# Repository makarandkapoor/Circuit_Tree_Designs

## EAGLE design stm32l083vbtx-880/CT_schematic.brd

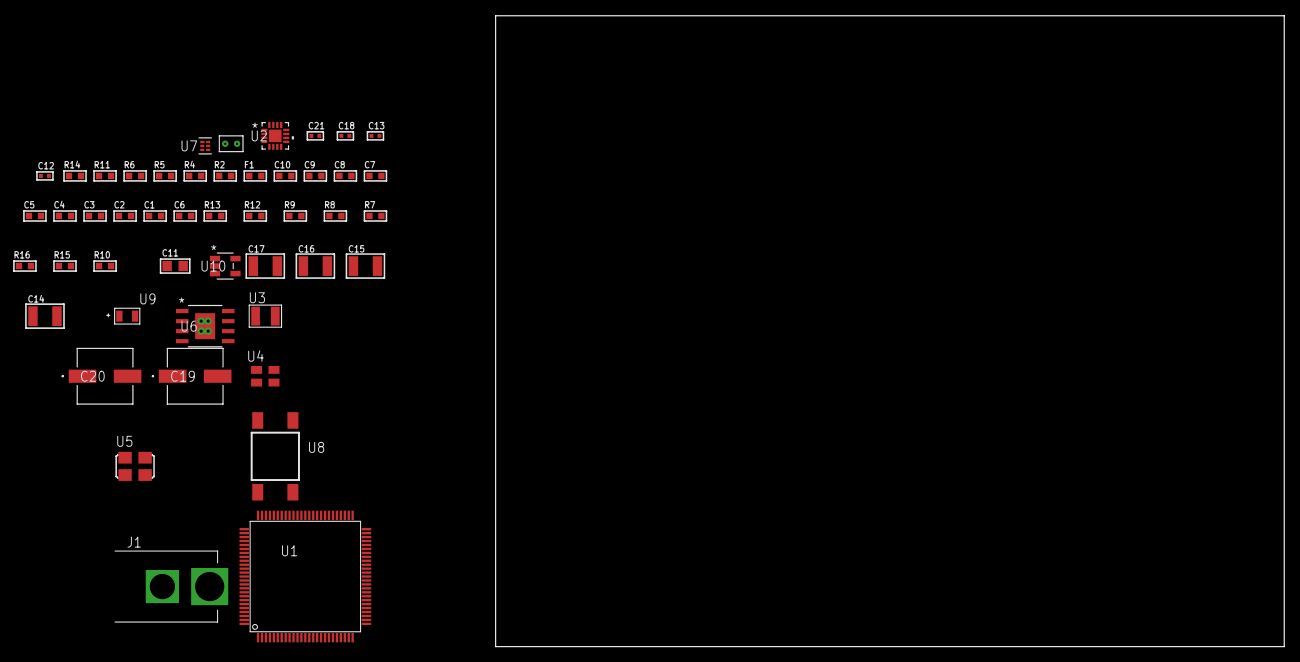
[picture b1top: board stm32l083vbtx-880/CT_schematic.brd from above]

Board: 2 copper layers, 100.0 x 80.0 mm, 48 parts (0 on the bottom side), 22 nets, no tracks yet.

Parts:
C1, C2, C3, C4, C5, C7, C10: 1e-07; C0603
C6: 4.7e-06; C0603
C8: 1e-08; C0603
C9: 1e-06; C0603
C11: 4.7e-06; C0805
C12, C13, C21: 1e-08; C0402
C14, C15, C16, C17: 1e-05; C1210
C18: 1e-07; C0402
C19, C20: 0.0001; EXV-9H
F1: 240.0; L0603
J1: PJ-037B; PJ-037B_PACKAGE
R2: 1000.0; R0603
R4: 4700.0; R0603
R5, R6, R11: 2200.0; R0603
R7, R8, R9, R12, R13: 10000.0; R0603
R10: 4031.5447154472; R0603
R14: 9100.0; R0603
R15: 680000.0; R0603
R16: 120000.0; R0603
U1: STM32L083VBT6; LQFP100
U2: M41T65Q6F; M41T65_QFN-16
U3: ABS07-32.768KHZ-7-T
U4: ASEK-32.768KHz-ECST; ASEK
U5: ASFL1-25MHZ-NCS; ASFL1
U6: MIC5234YME; SOIC-8_EP
U7: TPS3895ADRYR; SON-6
U8: 4-1437565-2; SW_4-1437565-2
U9: Q65110A2395; LGM67K-G1J2-24-Z
U10: nc7sz125m5x; NC7SZ125M5X
U11: Dummy; DUMMY_PACKAGE_100

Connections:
CLK_CRYSTAL_U2_1: U2.1, U3.1
CLK_CRYSTAL_U2_2: U2.2, U3.2
CLK_U1_8: U1.8, U4.3
CLK_U1_12: U1.12, U5.3
GND: C1.2, C2.2, C3.2, C4.2, C5.2, C6.2, C7.2, C8.2, C9.2, C10.2, C11.2, C12.2, C13.2, C14.2, C15.2, C16.2, C17.2, C18.2, C19.2, C20.2, C21.2, J1.2, R2.2, R7.2, R11.2, R14.2, R16.2, U1.19, U1.20, U1.27, U1.49, U1.74, U1.99, U2.3, U2.5, U2.17, U4.2, U5.2, U6.7, U6.EPAD, U7.2, U9.C, U10.1, U10.3, U11.1
NET_U1_6: C7.1, U1.6
NET_U1_14: R4.1, U1.14, U10.4
NET_U1_22: C8.1, C9.1, F1.1, U1.21, U1.22
NET_U1_68: R5.1, U1.68, U2.10
NET_U1_69: R6.1, U1.69, U2.9
NET_U1_94: R7.1, U1.94
NET_U1_98: U8.3, U8.4
NET_U2_4: R8.1, U2.4
NET_U2_11: R9.1, U2.11
NET_U6_4: R10.2, R11.1, U6.4
NET_U7_1: R13.1, R14.1, U7.1
NET_U7_3: R15.2, R16.1, U7.3
NET_U7_4: R12.1, U7.4, U10.2
NET_U8_1: R2.1, U8.1, U8.2
PROC_DAC_OUT2: U1.30, U11.2
VCC_S1_13V3: C14.1, C15.1, C19.1, C20.1, J1.1, U6.5, U6.8
VCC_TIER1_3V3: C1.1, C2.1, C3.1, C4.1, C5.1, C6.1, C10.1, C11.1, C12.1, C13.1, C16.1, C17.1, C18.1, C21.1, F1.2, R4.2, R5.2, R6.2, R8.2, R9.2, R10.1, R12.2, R13.2, R15.1, U1.28, U1.50, U1.73, U1.75, U1.100, U2.14, U4.4, U5.4, U6.1, U7.6, U10.5

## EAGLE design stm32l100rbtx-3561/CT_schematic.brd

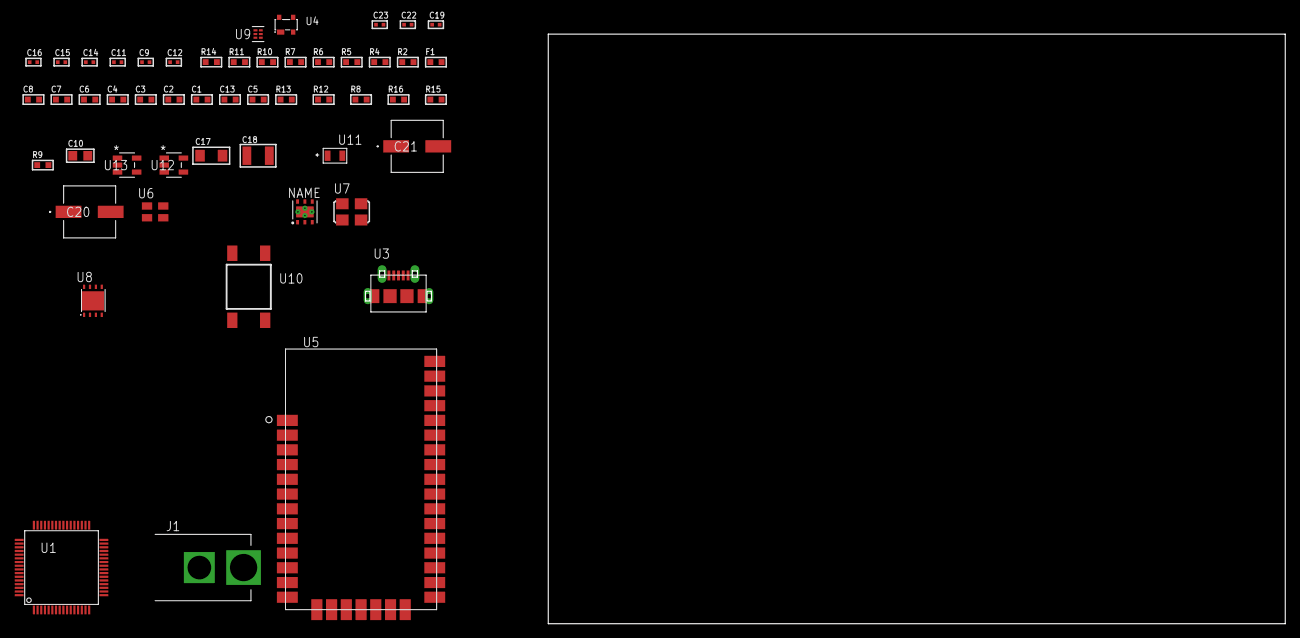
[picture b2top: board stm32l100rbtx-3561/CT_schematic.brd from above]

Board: 2 copper layers, 124.8 x 80.0 mm, 52 parts (0 on the bottom side), 27 nets, no tracks yet.

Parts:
C1, C2, C3, C4, C6: 1e-07; C0603
C5: 4.7e-06; C0603
C7: 1e-08; C0603
C8: 1e-06; C0603
C9, C14, C15, C16, C22, C23: 1e-08; C0402
C10: 1e-05; C0805
C11, C19: 1e-07; C0402
C12: 4.7e-11; C0402
C13: 8.2e-12; C0603
C17: 1e-05; C1206
C18: 1e-05; C1210
C20, C21: 0.0001; EXV-9H
F1: 240.0; L0603
J1: PJ-037B; PJ-037B_PACKAGE
R2, R11: 1000.0; R0603
R4, R5: 4700.0; R0603
R6, R7: 2200.0; R0603
R8, R12, R13: 10000.0; R0603
R9: 100000.0; R0603
R10: 2231.0; R0603
R14: 9100.0; R0603
R15: 680000.0; R0603
R16: 120000.0; R0603
U1: STM32L100RBT6; LQFP64
U2: HDC1080DMBR; WSON-6
U3: 47590-0001; MICRO_USB_AB
U4: prtr5v0u2ax; SOT143B
U5: XB24CZ7UIS-004
U6: ASEK-32.768KHz-ECST; ASEK
U7: ASFL1-25MHZ-NCS; ASFL1
U8: LP3878SDX-ADJ/NOPB; WSON-8
U9: TPS3895ADRYR; SON-6
U10: 4-1437565-2; SW_4-1437565-2
U11: Q65110A2395; LGM67K-G1J2-24-Z
U12, U13: nc7sz125m5x; NC7SZ125M5X

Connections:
CLK_U1_3: U1.3, U6.3
CLK_U1_5: U1.5, U7.3
GND: C1.2, C2.2, C3.2, C4.2, C5.2, C6.2, C7.2, C8.2, C9.2, C10.2, C11.2, C12.2, C13.2, C14.2, C15.2, C16.2, C17.2, C18.2, C19.2, C20.2, C21.2, C22.2, C23.2, J1.2, R2.2, R8.2, R11.2, R14.2, R16.2, U1.12, U1.18, U1.31, U1.47, U1.63, U2.2, U2.PAD, U3.5, U3.6, U3.7, U3.8, U3.9, U4.1, U5.1, U5.11, U5.13, U5.22, U5.35, U6.2, U7.2, U8.3, U8.PAD, U9.2, U11.C, U12.1, U12.3, U13.1, U13.3
NET_U1_1: C6.1, U1.1
NET_U1_7: R5.1, U1.7, U13.4
NET_U1_13: C7.1, C8.1, F1.1, U1.13
NET_U1_58: R6.1, U1.58, U2.6
NET_U1_59: R7.1, U1.59, U2.1
NET_U1_60: R8.1, U1.60
NET_U1_62: U10.3, U10.4
NET_U4_4: U3.1, U4.4
NET_U5_6: R4.1, U5.6, U12.4
NET_U8_1: C16.1, U8.1
NET_U8_6: R10.2, R11.1, U8.6
NET_U8_8: R9.1, U8.8
NET_U9_1: R13.1, R14.1, U9.1
NET_U9_3: R15.2, R16.1, U9.3
NET_U9_4: R12.1, U9.4, U12.2, U13.2
NET_U10_1: R2.1, U10.1, U10.2
PROC_SPI1_MISO: U1.22, U5.17
PROC_SPI1_MOSI: U1.23, U5.16
PROC_SPI1_NSS: U1.20, U5.15
PROC_SPI1_SCK: U1.21, U5.14
PROC_USB_DM: U1.44, U3.2, U4.3
PROC_USB_DP: U1.45, U3.3, U4.2
VCC_S1_5V9: C17.1, C20.1, C21.1, J1.1, R9.2, U8.4
VCC_TIER1_3V3: C1.1, C2.1, C3.1, C4.1, C5.1, C9.1, C10.1, C11.1, C12.1, C13.1, C14.1, C15.1, C18.1, C19.1, C22.1, C23.1, F1.2, R4.2, R5.2, R6.2, R7.2, R10.1, R12.2, R13.2, R15.1, U1.19, U1.32, U1.48, U1.64, U2.5, U5.2, U5.27, U6.4, U7.4, U8.5, U9.6, U12.5, U13.5

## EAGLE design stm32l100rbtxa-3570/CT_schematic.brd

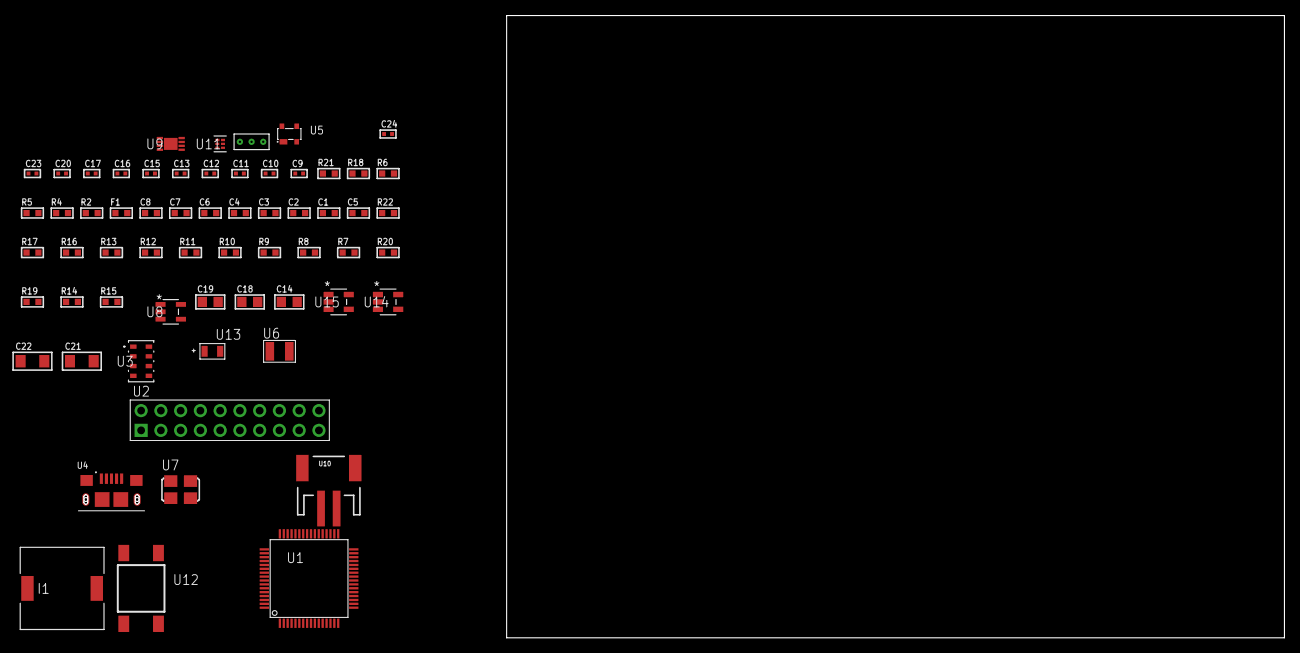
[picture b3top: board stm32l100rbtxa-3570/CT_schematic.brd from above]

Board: 2 copper layers, 154.3 x 80.0 mm, 62 parts (0 on the bottom side), 35 nets, no tracks yet.

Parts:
C1, C2, C3, C4, C6: 1e-07; C0603
C5: 4.7e-06; C0603
C7: 1e-08; C0603
C8: 1e-06; C0603
C9, C10: 1e-11; C0402
C11, C12, C13, C15, C16, C20: 1e-07; C0402
C14, C18, C19: 1e-05; C0805
C17, C23, C24: 1e-08; C0402
C21, C22: 1e-05; C1206
F1: 240.0; L0603
I1: 3.8e-06; DR1040
R2: 1000.0; R0603
R4: 4700.0; R0603
R5, R6: 2200.0; R0603
R7, R8, R9, R10, R11, R12, R13, R16, R17, R22: 10000.0; R0603
R14: 220000.0; R0603
R15: 1000000.0; R0603
R18: 9100.0; R0603
R19: 680000.0; R0603
R20: 120000.0; R0603
R21: 2000.0; R0603
U1: STM32L100RBT6A; LQFP64
U2: TST-110-05-T-D-RA
U3: MPL3115A2R1; LGA-8
U4: 10118193-0001LF; FCI_10118193-0001LF
U5: prtr5v0u2ax; SOT143B
U6: ABS07-32.768KHZ-7-T
U7: ASFL1-25MHZ-NCS; ASFL1
U8: ltc3406es5; TSOT-23-5
U9: MCP73831T-2ACI/MC; DFN8_2X3MC
U10: S2B-PH-SM4-TB(LF)(SN); JST-2-SMD
U11: TPS3895ADRYR; SON-6
U12: 4-1437565-2; SW_4-1437565-2
U13: Q65110A2395; LGM67K-G1J2-24-Z
U14, U15: nc7sz125m5x; NC7SZ125M5X
U16: Dummy; DUMMY_PACKAGE_135

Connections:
CLK_CRYSTAL_U1_3: C9.1, U1.3, U6.1
CLK_CRYSTAL_U1_4: C10.1, U1.4, U6.2
CLK_U1_5: U1.5, U7.3
GND: C1.2, C2.2, C3.2, C4.2, C5.2, C6.2, C7.2, C8.2, C9.2, C10.2, C11.2, C12.2, C13.2, C14.2, C15.2, C16.2, C17.2, C18.2, C19.1, C19.2, C20.2, C21.2, C22.2, C23.2, C24.2, R2.2, R7.2, R13.2, R14.2, R18.2, R20.2, R21.2, U1.12, U1.18, U1.31, U1.47, U1.63, U2.4, U2.6, U2.8, U2.10, U2.12, U2.14, U2.16, U2.18, U2.20, U3.3, U4.5, U4.6, U4.7, U4.8, U4.9, U5.1, U7.2, U8.2, U9.6, U9.9, U10.2, U11.2, U13.C, U14.2, U14.3, U15.1, U15.3, U16.1
INPUT_USBPOWER_5V: C21.1, R22.2, U4.1, U5.4, U9.1, U9.2
NET_U1_1: C6.1, U1.1
NET_U1_7: R4.1, U1.7, U15.4
NET_U1_13: C7.1, C8.1, F1.1, U1.13
NET_U1_58: R5.1, U1.58, U3.8
NET_U1_59: R6.1, U1.59, U3.7
NET_U1_60: R7.1, U1.60
NET_U1_62: U12.3, U12.4
NET_U2_19: R13.1, U2.19
NET_U3_2: C16.1, U3.2
NET_U8_3: I1.1, U8.3
NET_U8_5: R14.1, R15.1, U8.5
NET_U8_ATNET_3: I1.2, R15.2
NET_U9_5: R22.1, U9.5
NET_U9_8: R21.1, U9.8
NET_U11_1: R17.1, R18.1, U11.1
NET_U11_3: R19.2, R20.1, U11.3
NET_U11_4: R16.1, U11.4, U14.4, U15.2
NET_U12_1: R2.1, U12.1, U12.2
PROC_ADC_IN13: U1.11, U16.3
PROC_ADC_IN20: U1.35, U16.2
PROC_SYS_JTCK_SWCLK: R11.1, U1.49, U2.9
PROC_SYS_JTDI: R9.1, U1.50, U2.5
PROC_SYS_JTDO_TRACESWO: U1.55, U2.13
PROC_SYS_JTMS_SWDIO: R10.1, U1.46, U2.7
PROC_SYS_JTRST: R8.1, U1.56, U2.3
PROC_USB_DM: U1.44, U4.2, U5.3
PROC_USB_DP: U1.45, U4.3, U5.2
RST_OUT_U2_SRESET_B: R12.1, U2.15, U14.1
VCC_S1_3V7: C18.1, C22.1, U8.4, U9.3, U9.4, U10.1
VCC_TIER1_3V3: C1.1, C2.1, C3.1, C4.1, C5.1, C11.1, C12.1, C13.1, C14.1, C15.1, C17.1, C19.2, C20.1, C23.1, C24.1, F1.2, I1.2, R4.2, R5.2, R6.2, R8.2, R9.2, R10.2, R11.2, R12.2, R15.2, R16.2, R17.2, R19.1, U1.19, U1.32, U1.48, U1.64, U2.1, U2.2, U3.1, U3.4, U7.4, U11.6, U14.5, U15.5

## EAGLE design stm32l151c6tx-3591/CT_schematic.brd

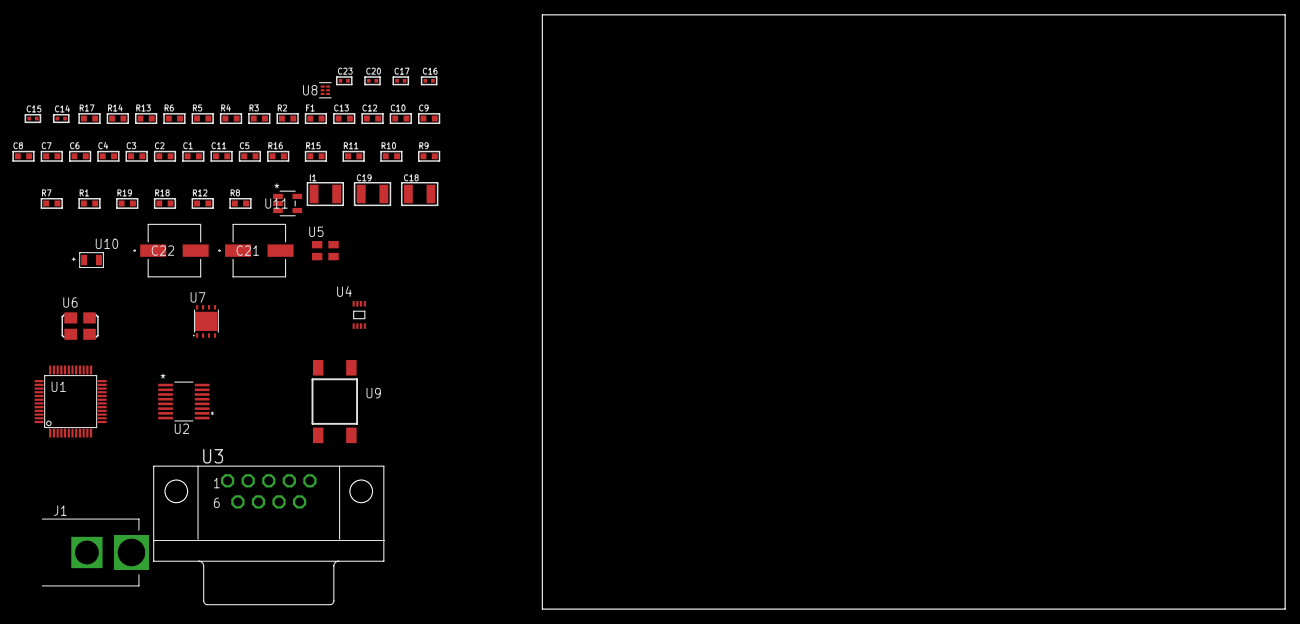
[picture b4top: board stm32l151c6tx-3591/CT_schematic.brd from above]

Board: 2 copper layers, 100.0 x 80.0 mm, 56 parts (0 on the bottom side), 36 nets, no tracks yet.

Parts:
C1, C2, C3, C4, C6: 1e-07; C0603
C5: 4.7e-06; C0603
C7: 1e-08; C0603
C8, C9, C10, C12, C13: 1e-06; C0603
C11: 2.2e-07; C0603
C14, C15, C16, C17, C23: 1e-08; C0402
C18, C19: 1e-05; C1210
C20: 1e-07; C0402
C21, C22: 0.0001; EXV-9H
F1: 240.0; L0603
I1: 1e-05; L1210
J1: PJ-037B; PJ-037B_PACKAGE
R1, R7, R9, R10, R11, R15, R16: 10000.0; R0603
R2, R14: 1000.0; R0603
R3: 1600.5; R0603
R4: 4700.0; R0603
R5, R6: 2200.0; R0603
R8, R12: 100000.0; R0603
R13: 2231.0; R0603
R17: 9100.0; R0603
R18: 680000.0; R0603
R19: 120000.0; R0603
U1: STM32L151C6T6; LQFP48
U2: LTC2804CGN-1#PBF; SSOP-16
U3: 182-009-113R531; 182-009-MALE
U4: 24AA128T-I/MNY; TDFN-8/6MM
U5: ASEK-32.768KHz-ECST; ASEK
U6: ASFL1-25MHZ-NCS; ASFL1
U7: LP3878SDX-ADJ/NOPB; WSON-8
U8: TPS3895ADRYR; SON-6
U9: 4-1437565-2; SW_4-1437565-2
U10: Q65110A2395; LGM67K-G1J2-24-Z
U11: nc7sz125m5x; NC7SZ125M5X

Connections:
CLK_U1_3: U1.3, U5.3
CLK_U1_5: U1.5, U6.3
GND: C1.2, C2.2, C3.2, C4.2, C5.2, C6.2, C7.2, C8.2, C9.2, C10.2, C12.2, C13.2, C14.2, C15.2, C16.2, C17.2, C18.2, C19.2, C20.2, C21.2, C22.2, C23.2, J1.2, R2.2, R7.2, R11.2, R14.2, R17.2, R19.2, U1.8, U1.23, U1.35, U1.47, U2.8, U3.5, U4.4, U5.2, U6.2, U7.3, U7.PAD, U8.2, U10.C, U11.1, U11.3
NET_U1_1: C6.1, U1.1
NET_U1_7: R4.1, U1.7, U11.4
NET_U1_9: C7.1, C8.1, F1.1, U1.9
NET_U1_42: R5.1, U1.42, U4.6
NET_U1_43: R6.1, U1.43, U4.5
NET_U1_44: R7.1, U1.44
NET_U1_45: R3.1, U1.45, U10.A
NET_U1_46: R1.1, U1.46, U9.3, U9.4
NET_U2_6: C9.1, U2.6
NET_U2_7: C11.1, I1.2, U2.7
NET_U2_9: C10.1, U2.9
NET_U2_10: C11.2, U2.10
NET_U2_11: R8.1, U2.11
NET_U3_2: U2.1, U3.2
NET_U3_3: U2.3, U3.3
NET_U3_7: U2.2, U3.7
NET_U3_8: U2.4, U3.8
NET_U4_1: R9.1, U4.1
NET_U4_2: R10.1, U4.2
NET_U4_3: R11.1, U4.3
NET_U7_1: C17.1, U7.1
NET_U7_6: R13.2, R14.1, U7.6
NET_U7_8: R12.1, U7.8
NET_U8_1: R16.1, R17.1, U8.1
NET_U8_3: R18.2, R19.1, U8.3
NET_U8_4: R15.1, U8.4, U11.2
NET_U9_1: R2.1, U9.1, U9.2
PROC_USART1_CTS: U1.32, U2.13
PROC_USART1_RTS: U1.33, U2.15
PROC_USART1_RX: U1.31, U2.16
PROC_USART1_TX: U1.30, U2.14
VCC_S1_13V8: C18.1, C21.1, C22.1, J1.1, R12.2, U7.4
VCC_TIER1_3V3: C1.1, C2.1, C3.1, C4.1, C5.1, C12.1, C13.1, C14.1, C15.1, C16.1, C19.1, C20.1, C23.1, F1.2, I1.1, R1.2, R3.2, R4.2, R5.2, R6.2, R8.2, R9.2, R10.2, R13.1, R15.2, R16.2, R18.1, U1.24, U1.36, U1.48, U2.5, U2.12, U4.7, U4.8, U5.4, U6.4, U7.5, U8.6, U11.5

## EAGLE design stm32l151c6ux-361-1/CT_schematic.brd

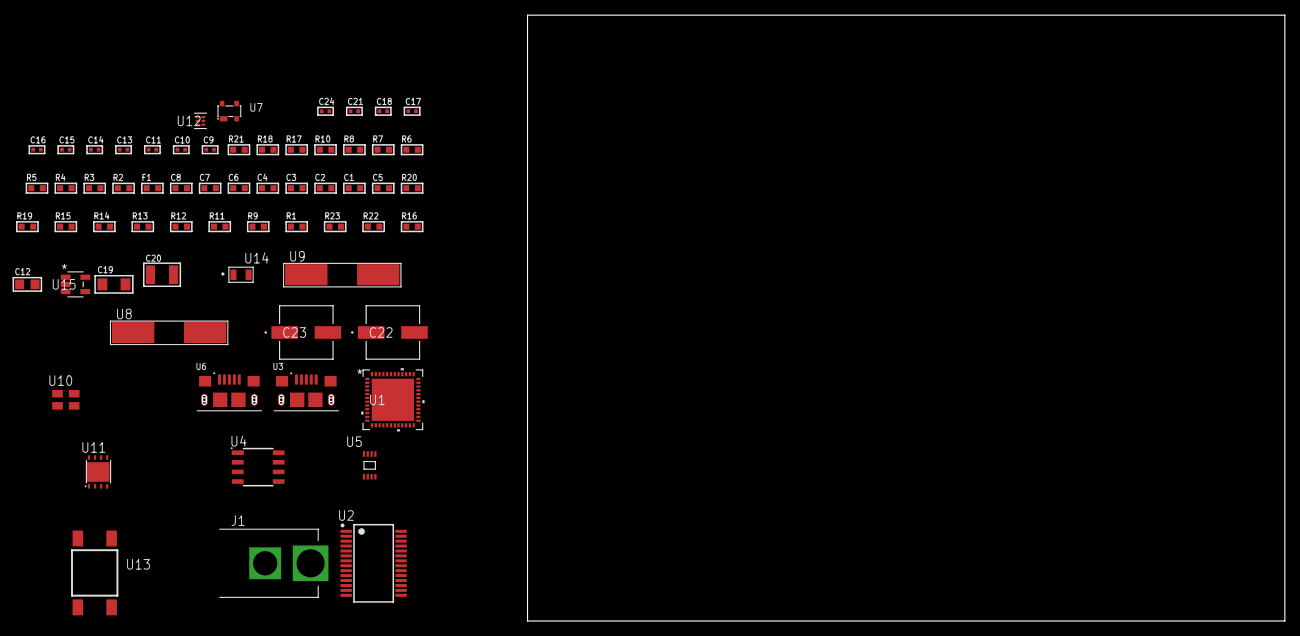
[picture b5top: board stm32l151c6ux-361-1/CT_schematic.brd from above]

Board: 2 copper layers, 64 parts (0 on the bottom side), 41 nets, no tracks yet.

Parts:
C1, C2, C3, C4, C6: 1e-07; C0603
C5: 4.7e-06; C0603
C7: 1e-08; C0603
C8: 1e-06; C0603
C9, C10: 1e-11; C0402
C11, C13, C14, C21: 1e-07; C0402
C12: 4.7e-06; C0805
C15, C16, C17, C18, C24: 1e-08; C0402
C19: 1e-05; C1206
C20: 1e-05; C1210
C22, C23: 0.0001; EXV-9H
F1: 240.0; L0603
J1: PJ-037B; PJ-037B_PACKAGE
R1, R9, R11, R12, R13, R14, R15, R19, R20: 10000.0; R0603
R2, R18: 1000.0; R0603
R3: 1600.5; R0603
R4, R10: 4700.0; R0603
R5, R6, R7, R8: 2200.0; R0603
R16: 100000.0; R0603
R17: 2231.0; R0603
R21: 9100.0; R0603
R22: 680000.0; R0603
R23: 120000.0; R0603
U1: STM32L151C6U6; UFQFPN48
U2: FT232RL-REEL; SSOP-28
U3, U6: 10118193-0001LF; FCI_10118193-0001LF
U4: 24AA1025T-I/SN; SOIC-8
U5: 24AA16-I/MC; TDFN-8/6MM
U7: prtr5v0u2ax; SOT143B
U8: ABLS-25.000MHZ-B2F-T
U9: ABLS-12.000MHZ-B4-T
U10: ASEK-32.768KHz-ECST; ASEK
U11: LP3878SDX-ADJ/NOPB; WSON-8
U12: TPS3895ADRYR; SON-6
U13: 4-1437565-2; SW_4-1437565-2
U14: Q65110A2395; LGM67K-G1J2-24-Z
U15: nc7sz125m5x; NC7SZ125M5X

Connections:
CLK_CRYSTAL_U1_5: C9.1, U1.5, U8.1
CLK_CRYSTAL_U1_6: C10.1, U1.6, U8.2
CLK_CRYSTAL_U2_27: U2.27, U9.1
CLK_CRYSTAL_U2_28: U2.28, U9.2
CLK_U1_3: U1.3, U10.3
GND: C1.2, C2.2, C3.2, C4.2, C5.2, C6.2, C7.2, C8.2, C9.2, C10.2, C11.2, C12.2, C13.2, C14.2, C15.2, C16.2, C17.2, C18.2, C19.2, C20.2, C21.2, C22.2, C23.2, C24.2, J1.2, R2.2, R9.2, R12.2, R18.2, R21.2, R23.2, U1.8, U1.23, U1.35, U1.47, U1.49, U2.7, U2.18, U2.21, U2.25, U2.26, U3.5, U3.6, U3.7, U3.8, U3.9, U4.4, U4.7, U5.4, U6.5, U6.6, U6.7, U6.8, U6.9, U7.1, U10.2, U11.3, U11.PAD, U12.2, U14.C, U15.1, U15.3
NET_U1_1: C6.1, U1.1
NET_U1_7: R4.1, U1.7, U15.4
NET_U1_9: C7.1, C8.1, F1.1, U1.9
NET_U1_21: R7.1, U1.21, U5.6
NET_U1_22: R8.1, U1.22, U5.5
NET_U1_42: R5.1, U1.42, U4.6
NET_U1_43: R6.1, U1.43, U4.5
NET_U1_44: R9.1, U1.44
NET_U1_45: R3.1, U1.45, U14.A
NET_U1_46: R1.1, U1.46, U13.3, U13.4
NET_U2_14: R11.1, U2.14
NET_U2_17: C13.1, U2.17
NET_U2_19: R12.1, U2.19
NET_U3_1: R10.1, U3.1
NET_U3_2: U2.16, U3.2
NET_U3_3: U2.15, U3.3
NET_U4_1: R14.1, U4.1
NET_U4_2: R15.1, U4.2
NET_U4_3: R13.1, U4.3
NET_U7_4: U6.1, U7.4
NET_U11_1: C18.1, U11.1
NET_U11_6: R17.2, R18.1, U11.6
NET_U11_8: R16.1, U11.8
NET_U12_1: R20.1, R21.1, U12.1
NET_U12_3: R22.2, R23.1, U12.3
NET_U12_4: R19.1, U12.4, U15.2
NET_U13_1: R2.1, U13.1, U13.2
PROC_USART2_CTS: U1.10, U2.3
PROC_USART2_RTS: U1.11, U2.11
PROC_USART2_RX: U1.13, U2.1
PROC_USART2_TX: U1.12, U2.5
PROC_USB_DM: U1.32, U6.2, U7.3
PROC_USB_DP: U1.33, U6.3, U7.2
VCC_S1_8V1: C19.1, C22.1, C23.1, J1.1, R16.2, U11.4
VCC_TIER1_3V3: C1.1, C2.1, C3.1, C4.1, C5.1, C11.1, C12.1, C14.1, C15.1, C16.1, C17.1, C20.1, C21.1, C24.1, F1.2, R1.2, R3.2, R4.2, R5.2, R6.2, R7.2, R8.2, R11.2, R13.2, R14.2, R15.2, R17.1, R19.2, R20.2, R22.1, U1.24, U1.36, U1.48, U2.4, U2.20, U4.8, U5.7, U5.8, U10.4, U11.5, U12.6, U15.5

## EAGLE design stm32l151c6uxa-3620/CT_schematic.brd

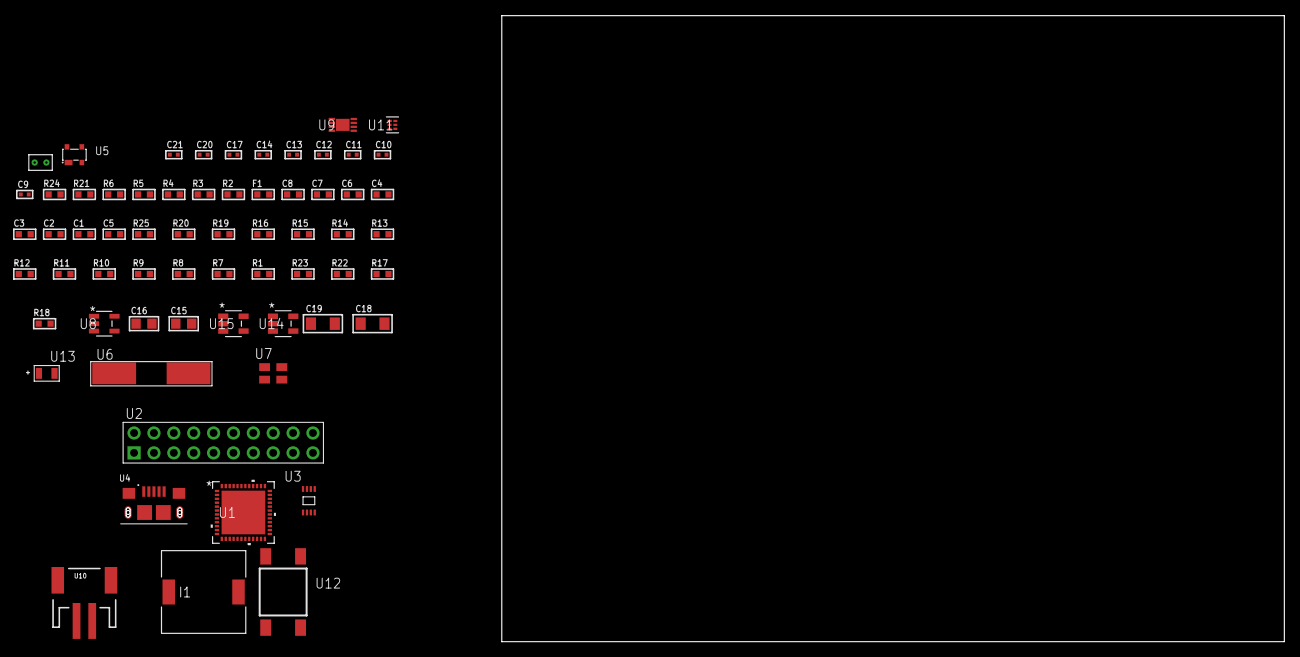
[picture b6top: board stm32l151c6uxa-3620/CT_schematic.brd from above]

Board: 2 copper layers, 64 parts (0 on the bottom side), 37 nets, no tracks yet.

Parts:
C1, C2, C3, C4, C6: 1e-07; C0603
C5: 4.7e-06; C0603
C7: 1e-08; C0603
C8: 1e-06; C0603
C9, C10: 1e-11; C0402
C11, C12, C17: 1e-07; C0402
C13, C14, C20, C21: 1e-08; C0402
C15, C16: 1e-05; C0805
C18, C19: 1e-05; C1206
F1: 240.0; L0603
I1: 3.8e-06; DR1040
R1, R7, R8, R9, R10, R11, R12, R13, R14, R15, R16, R19, R20, R25: 10000.0; R0603
R2: 1000.0; R0603
R3: 1600.5; R0603
R4: 4700.0; R0603
R5, R6: 2200.0; R0603
R17: 220000.0; R0603
R18: 1000000.0; R0603
R21: 9100.0; R0603
R22: 680000.0; R0603
R23: 120000.0; R0603
R24: 2000.0; R0603
U1: STM32L151C6U6A; UFQFPN48
U2: TST-110-05-T-D-RA
U3: 24AA128T-I/MNY; TDFN-8/6MM
U4: 10118193-0001LF; FCI_10118193-0001LF
U5: prtr5v0u2ax; SOT143B
U6: ABLS-25.000MHZ-B2F-T
U7: ASEK-32.768KHz-ECST; ASEK
U8: ltc3406es5; TSOT-23-5
U9: MCP73831T-2ACI/MC; DFN8_2X3MC
U10: S2B-PH-SM4-TB(LF)(SN); JST-2-SMD
U11: TPS3895ADRYR; SON-6
U12: 4-1437565-2; SW_4-1437565-2
U13: Q65110A2395; LGM67K-G1J2-24-Z
U14, U15: nc7sz125m5x; NC7SZ125M5X
U16: Dummy; DUMMY_PACKAGE_136

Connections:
CLK_CRYSTAL_U1_5: C9.1, U1.5, U6.1
CLK_CRYSTAL_U1_6: C10.1, U1.6, U6.2
CLK_U1_3: U1.3, U7.3
GND: C1.2, C2.2, C3.2, C4.2, C5.2, C6.2, C7.2, C8.2, C9.2, C10.2, C11.2, C12.2, C13.2, C14.2, C15.2, C16.1, C16.2, C17.2, C18.2, C19.2, C20.2, C21.2, R2.2, R7.2, R13.2, R14.2, R17.2, R21.2, R23.2, R24.2, U1.8, U1.23, U1.35, U1.47, U1.49, U2.4, U2.6, U2.8, U2.10, U2.12, U2.14, U2.16, U2.18, U2.20, U3.4, U3.7, U4.5, U4.6, U4.7, U4.8, U4.9, U5.1, U7.2, U8.2, U9.6, U9.9, U10.2, U11.2, U13.C, U14.2, U14.3, U15.1, U15.3, U16.1
INPUT_USBPOWER_5V: C18.1, R25.2, U4.1, U5.4, U9.1, U9.2
NET_U1_1: C6.1, U1.1
NET_U1_7: R4.1, U1.7, U15.4
NET_U1_9: C7.1, C8.1, F1.1, U1.9
NET_U1_42: R5.1, U1.42, U3.6
NET_U1_43: R6.1, U1.43, U3.5
NET_U1_44: R7.1, U1.44
NET_U1_45: R3.1, U1.45, U13.A
NET_U1_46: R1.1, U1.46, U12.3, U12.4
NET_U2_19: R13.1, U2.19
NET_U3_1: R14.1, U3.1
NET_U3_2: R15.1, U3.2
NET_U3_3: R16.1, U3.3
NET_U8_3: I1.1, U8.3
NET_U8_5: R17.1, R18.1, U8.5
NET_U8_ATNET_3: I1.2, R18.2
NET_U9_5: R25.1, U9.5
NET_U9_8: R24.1, U9.8
NET_U11_1: R20.1, R21.1, U11.1
NET_U11_3: R22.2, R23.1, U11.3
NET_U11_4: R19.1, U11.4, U14.4, U15.2
NET_U12_1: R2.1, U12.1, U12.2
PROC_DAC_OUT2: U1.15, U16.2
PROC_SYS_JTCK_SWCLK: R11.1, U1.37, U2.9
PROC_SYS_JTDI: R9.1, U1.38, U2.5
PROC_SYS_JTDO_TRACESWO: U1.39, U2.13
PROC_SYS_JTMS_SWDIO: R10.1, U1.34, U2.7
PROC_SYS_JTRST: R8.1, U1.40, U2.3
PROC_USB_DM: U1.32, U4.2, U5.3
PROC_USB_DP: U1.33, U4.3, U5.2
RST_OUT_U2_SRESET_B: R12.1, U2.15, U14.1
VCC_S1_3V7: C15.1, C19.1, U8.4, U9.3, U9.4, U10.1
VCC_TIER1_3V3: C1.1, C2.1, C3.1, C4.1, C5.1, C11.1, C12.1, C13.1, C14.1, C16.2, C17.1, C20.1, C21.1, F1.2, I1.2, R1.2, R3.2, R4.2, R5.2, R6.2, R8.2, R9.2, R10.2, R11.2, R12.2, R15.2, R16.2, R18.2, R19.2, R20.2, R22.1, U1.24, U1.36, U1.48, U2.1, U2.2, U3.8, U7.4, U11.6, U14.5, U15.5

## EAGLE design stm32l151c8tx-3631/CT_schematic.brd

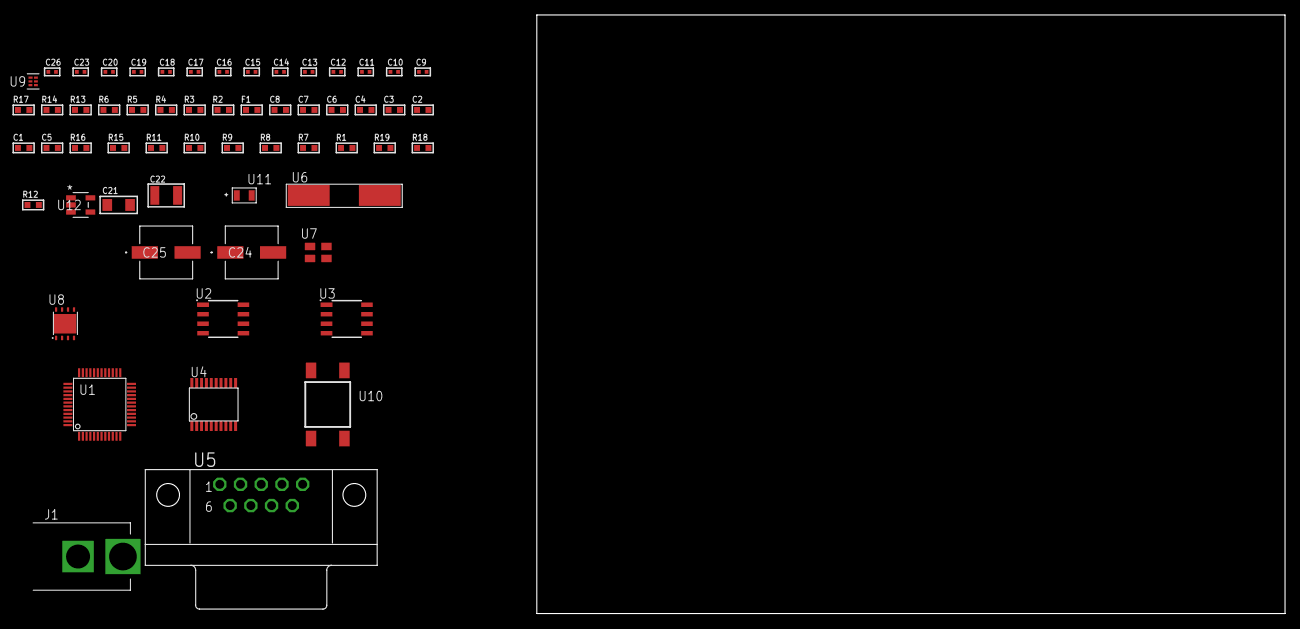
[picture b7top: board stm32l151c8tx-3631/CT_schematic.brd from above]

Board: 2 copper layers, 100.0 x 80.0 mm, 59 parts (0 on the bottom side), 42 nets, no tracks yet.

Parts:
C1, C2, C3, C4, C6: 1e-07; C0603
C5: 4.7e-06; C0603
C7: 1e-08; C0603
C8: 1e-06; C0603
C9, C10: 1e-11; C0402
C11, C12, C19, C20, C26: 1e-08; C0402
C13, C14, C15, C16, C17, C18, C23: 1e-07; C0402
C21: 1e-05; C1206
C22: 1e-05; C1210
C24, C25: 0.0001; EXV-9H
F1: 240.0; L0603
J1: PJ-037B; PJ-037B_PACKAGE
R1, R7, R8, R9, R10, R11, R15, R16: 10000.0; R0603
R2, R14: 1000.0; R0603
R3: 1600.5; R0603
R4: 4700.0; R0603
R5, R6: 2200.0; R0603
R12: 100000.0; R0603
R13: 2231.0; R0603
R17: 9100.0; R0603
R18: 680000.0; R0603
R19: 120000.0; R0603
U1: STM32L151C8T6; LQFP48
U2: AT25040B-SSHL-T; SOIC-8
U3: M24M02-DRMN6TP; SOIC-8
U4: SP3203ECY-L/TR; TSSOP20-I
U5: 182-009-113R531; 182-009-MALE
U6: ABLS-25.000MHZ-B2F-T
U7: ASEK-32.768KHz-ECST; ASEK
U8: LP3878SDX-ADJ/NOPB; WSON-8
U9: TPS3895ADRYR; SON-6
U10: 4-1437565-2; SW_4-1437565-2
U11: Q65110A2395; LGM67K-G1J2-24-Z
U12: nc7sz125m5x; NC7SZ125M5X

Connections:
CLK_CRYSTAL_U1_5: C9.1, U1.5, U6.1
CLK_CRYSTAL_U1_6: C10.1, U1.6, U6.2
CLK_U1_3: U1.3, U7.3
GND: C1.2, C2.2, C3.2, C4.2, C5.2, C6.2, C7.2, C8.2, C9.2, C10.2, C11.2, C12.2, C13.2, C14.2, C17.2, C18.2, C19.2, C20.2, C21.2, C22.2, C23.2, C24.2, C25.2, C26.2, J1.2, R2.2, R7.2, R11.2, R14.2, R17.2, R19.2, U1.8, U1.23, U1.35, U1.47, U2.4, U3.4, U4.18, U5.5, U7.2, U8.3, U8.PAD, U9.2, U11.C, U12.1, U12.3
NET_U1_1: C6.1, U1.1
NET_U1_7: R4.1, U1.7, U12.4
NET_U1_9: C7.1, C8.1, F1.1, U1.9
NET_U1_42: R5.1, U1.42, U3.6
NET_U1_43: R6.1, U1.43, U3.5
NET_U1_44: R7.1, U1.44
NET_U1_45: R3.1, U1.45, U11.A
NET_U1_46: R1.1, U1.46, U10.3, U10.4
NET_U2_3: R8.1, U2.3
NET_U2_7: R10.1, U2.7
NET_U3_3: R11.1, U3.3
NET_U4_1: C15.1, U4.1
NET_U4_2: C17.1, U4.2
NET_U4_3: C15.2, U4.3
NET_U4_4: C16.1, U4.4
NET_U4_5: C16.2, U4.5
NET_U4_6: C18.1, U4.6
NET_U5_2: U4.14, U5.2
NET_U5_3: U4.17, U5.3
NET_U5_7: U4.13, U5.7
NET_U5_8: U4.16, U5.8
NET_U8_1: C20.1, U8.1
NET_U8_6: R13.2, R14.1, U8.6
NET_U8_8: R12.1, U8.8
NET_U9_1: R16.1, R17.1, U9.1
NET_U9_3: R18.2, R19.1, U9.3
NET_U9_4: R15.1, U9.4, U12.2
NET_U10_1: R2.1, U10.1, U10.2
PROC_SPI1_MISO: U1.16, U2.2
PROC_SPI1_MOSI: U1.17, U2.5
PROC_SPI1_NSS: R9.1, U1.14, U2.1
PROC_SPI1_SCK: U1.15, U2.6
PROC_USART1_CTS: U1.32, U4.8
PROC_USART1_RTS: U1.33, U4.10
PROC_USART1_RX: U1.31, U4.11
PROC_USART1_TX: U1.30, U4.7
VCC_S1_11V0: C21.1, C24.1, C25.1, J1.1, R12.2, U8.4
VCC_TIER1_3V3: C1.1, C2.1, C3.1, C4.1, C5.1, C11.1, C12.1, C13.1, C14.1, C19.1, C22.1, C23.1, C26.1, F1.2, R1.2, R3.2, R4.2, R5.2, R6.2, R8.2, R9.2, R10.2, R13.1, R15.2, R16.2, R18.1, U1.24, U1.36, U1.48, U2.8, U3.8, U4.12, U4.19, U7.4, U8.5, U9.6, U12.5

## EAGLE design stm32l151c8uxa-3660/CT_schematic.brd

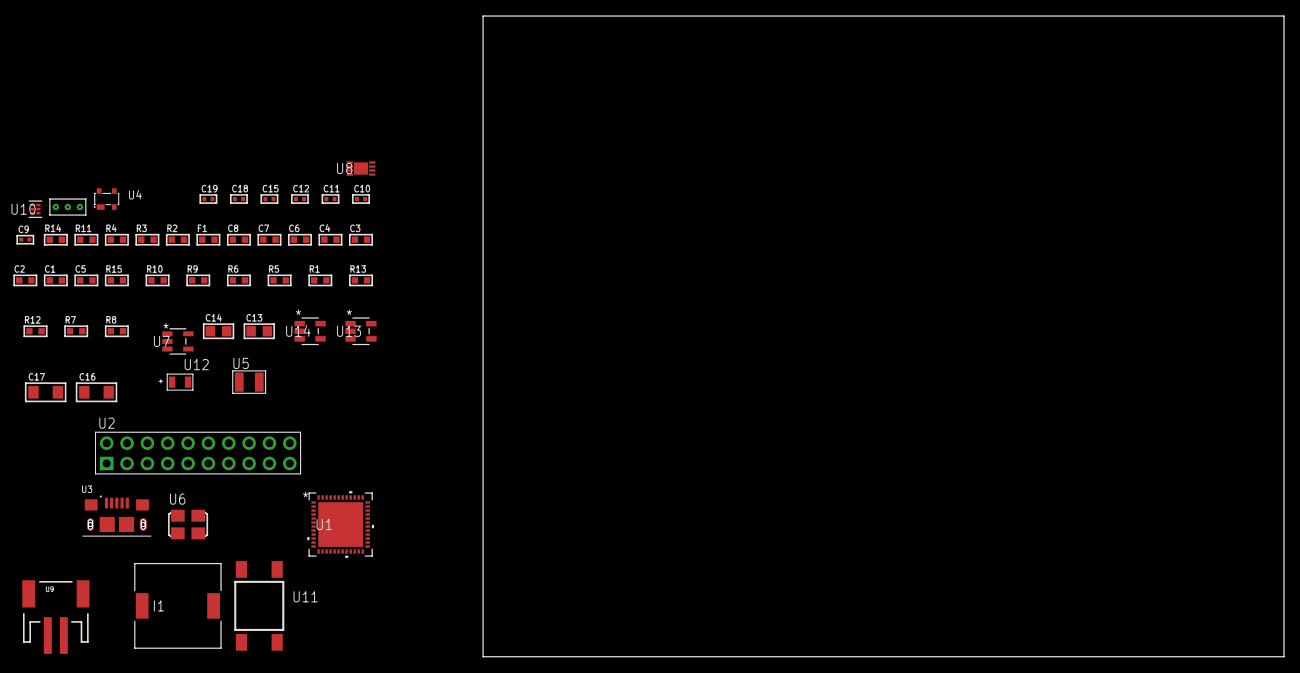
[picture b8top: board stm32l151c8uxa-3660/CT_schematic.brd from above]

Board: 2 copper layers, 149.3 x 80.0 mm, 51 parts (0 on the bottom side), 30 nets, no tracks yet.

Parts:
C1, C2, C3, C4, C6: 1e-07; C0603
C5: 4.7e-06; C0603
C7: 1e-08; C0603
C8: 1e-06; C0603
C9, C10: 1e-11; C0402
C11, C15: 1e-07; C0402
C12, C18, C19: 1e-08; C0402
C13, C14: 1e-05; C0805
C16, C17: 1e-05; C1206
F1: 240.0; L0603
I1: 3.8e-06; DR1040
R1, R5, R6, R9, R10, R15: 10000.0; R0603
R2: 1000.0; R0603
R3: 1600.5; R0603
R4: 4700.0; R0603
R7: 220000.0; R0603
R8: 1000000.0; R0603
R11: 9100.0; R0603
R12: 680000.0; R0603
R13: 120000.0; R0603
R14: 2000.0; R0603
U1: STM32L151C8U6A; UFQFPN48
U2: TST-110-05-T-D-RA
U3: 10118193-0001LF; FCI_10118193-0001LF
U4: prtr5v0u2ax; SOT143B
U5: ABS07-32.768KHZ-7-T
U6: ASFL1-25MHZ-NCS; ASFL1
U7: ltc3406es5; TSOT-23-5
U8: MCP73831T-2ACI/MC; DFN8_2X3MC
U9: S2B-PH-SM4-TB(LF)(SN); JST-2-SMD
U10: TPS3895ADRYR; SON-6
U11: 4-1437565-2; SW_4-1437565-2
U12: Q65110A2395; LGM67K-G1J2-24-Z
U13, U14: nc7sz125m5x; NC7SZ125M5X
U15: Dummy; DUMMY_PACKAGE_106

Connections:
CLK_CRYSTAL_U1_3: C9.1, U1.3, U5.1
CLK_CRYSTAL_U1_4: C10.1, U1.4, U5.2
CLK_U1_5: U1.5, U6.3
GND: C1.2, C2.2, C3.2, C4.2, C5.2, C6.2, C7.2, C8.2, C9.2, C10.2, C11.2, C12.2, C13.2, C14.1, C14.2, C15.2, C16.2, C17.2, C18.2, C19.2, R2.2, R5.2, R7.2, R11.2, R13.2, R14.2, U1.8, U1.23, U1.35, U1.47, U1.49, U2.4, U2.6, U2.8, U2.10, U2.12, U2.14, U2.16, U2.18, U2.20, U3.5, U3.6, U3.7, U3.8, U3.9, U4.1, U6.2, U7.2, U8.6, U8.9, U9.2, U10.2, U12.C, U13.2, U13.3, U14.1, U14.3, U15.1
INPUT_USBPOWER_5V: C16.1, R15.2, U3.1, U4.4, U8.1, U8.2
NET_U1_1: C6.1, U1.1
NET_U1_7: R4.1, U1.7, U14.4
NET_U1_9: C7.1, C8.1, F1.1, U1.9
NET_U1_44: R5.1, U1.44
NET_U1_45: R3.1, U1.45, U12.A
NET_U1_46: R1.1, U1.46, U11.3, U11.4
NET_U7_3: I1.1, U7.3
NET_U7_5: R7.1, R8.1, U7.5
NET_U7_ATNET_3: I1.2, R8.2
NET_U8_5: R15.1, U8.5
NET_U8_8: R14.1, U8.8
NET_U10_1: R10.1, R11.1, U10.1
NET_U10_3: R12.2, R13.1, U10.3
NET_U10_4: R9.1, U10.4, U13.4, U14.2
NET_U11_1: R2.1, U11.1, U11.2
PROC_SYS_JTCK_SWCLK: U1.37, U2.9
PROC_SYS_JTDO_TRACESWO: U1.39, U2.13
PROC_SYS_JTMS_SWDIO: U1.34, U2.7
PROC_TIM10_CH1: U1.16, U15.2
PROC_TIM11_CH1: U1.17, U15.3
PROC_USB_DM: U1.32, U3.2, U4.3
PROC_USB_DP: U1.33, U3.3, U4.2
RST_OUT_U2_SRESET_B: R6.1, U2.15, U13.1
VCC_S1_3V7: C13.1, C17.1, U7.4, U8.3, U8.4, U9.1
VCC_TIER1_3V3: C1.1, C2.1, C3.1, C4.1, C5.1, C11.1, C12.1, C14.2, C15.1, C18.1, C19.1, F1.2, I1.2, R1.2, R3.2, R4.2, R6.2, R8.2, R9.2, R10.2, R12.1, U1.24, U1.36, U1.48, U2.1, U6.4, U10.6, U13.5, U14.5
